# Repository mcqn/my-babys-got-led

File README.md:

# My Babys Got LED

An ESP8266 board to drive Neopixel/WS2812 LED strips, for plug-and-play use with an ATX power supply. The board is [OSHW certified](https://certification.oshwa.org/uk000030.html
). Latest version now has three injection points with 8A fuses for safety, to manage the high power of ATX power supplies.

See the [My Baby's Got LED product page](https://mcqn.com/ibal223) on the MCQN website for full details.

The finished product is available for sale on Tindie:

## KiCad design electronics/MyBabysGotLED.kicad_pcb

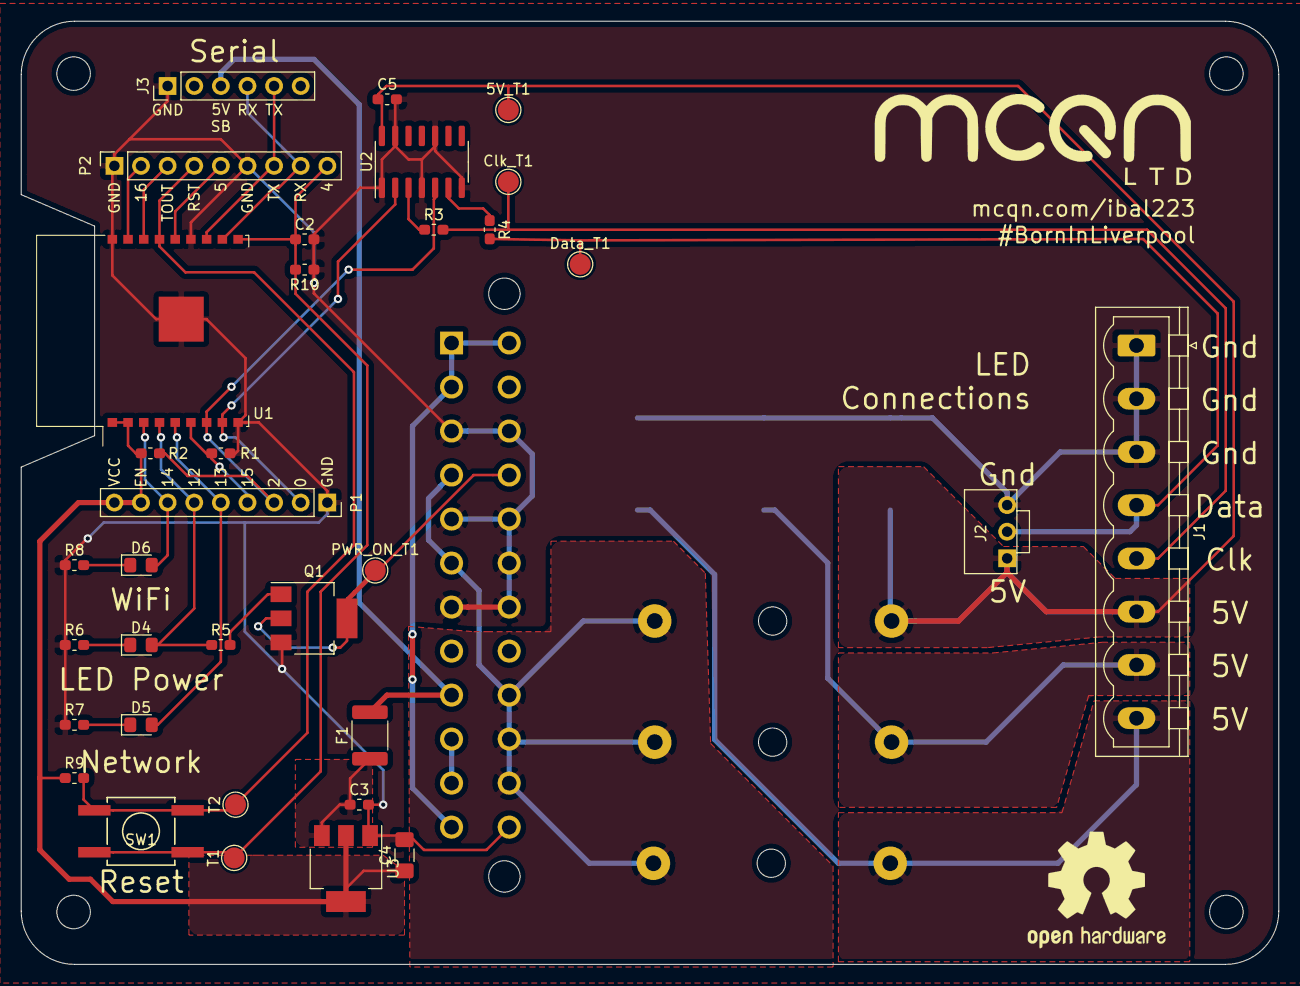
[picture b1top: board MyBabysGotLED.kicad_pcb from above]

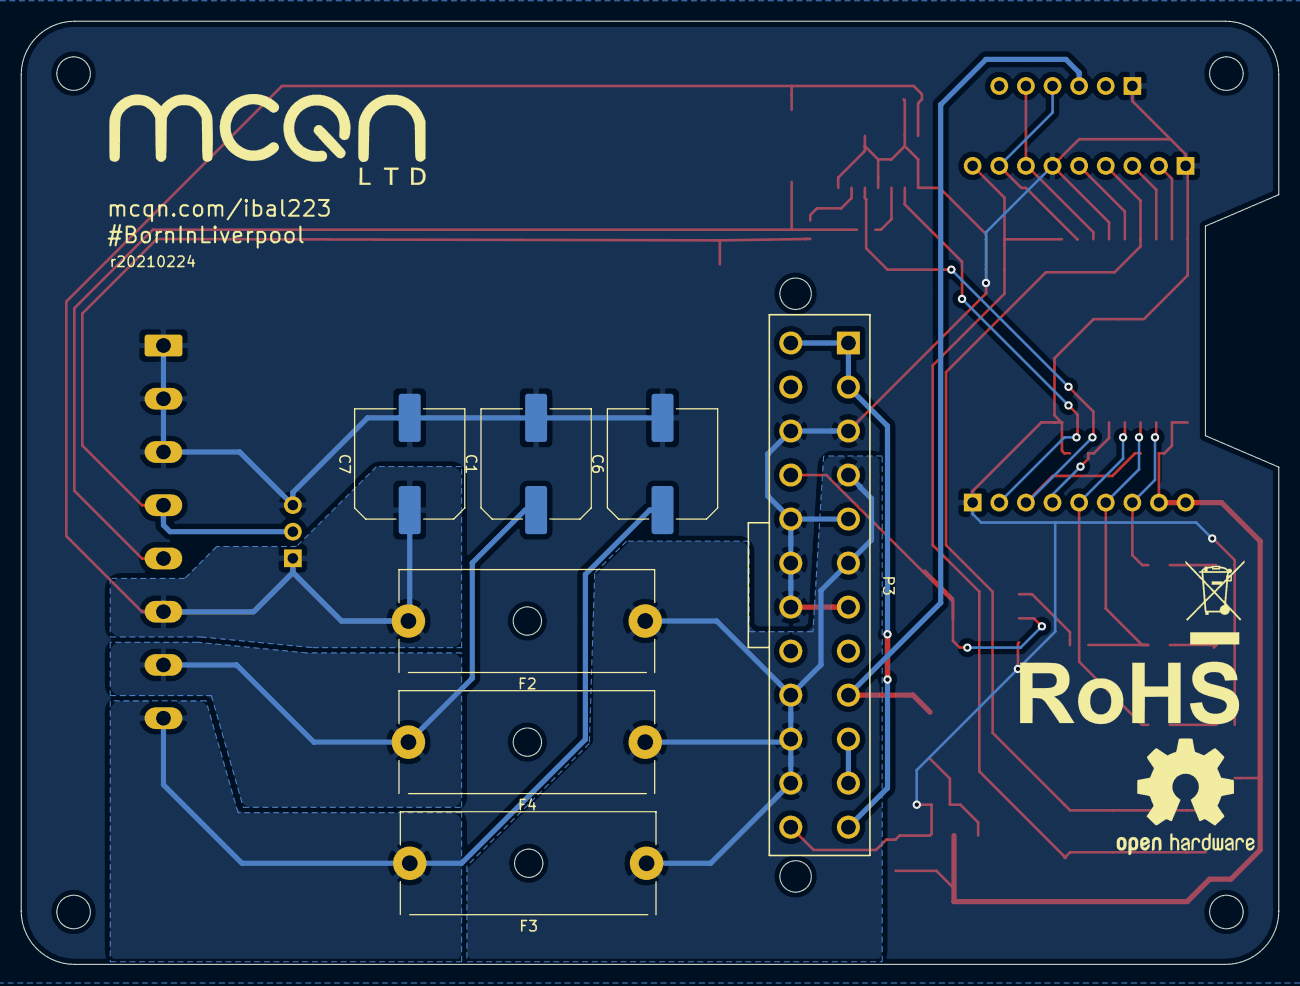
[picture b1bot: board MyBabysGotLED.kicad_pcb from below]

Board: 2 copper layers, 120.0 x 90.0 mm, 41 parts (7 on the bottom side), 32 nets.

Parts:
5V_T1: Conn_01x01; TestPoint_Pad_D2.0mm
C1, C6, C7: 470uF; C_Elec_10x10.2
C2: C47nF; C_0603_1608Metric_Pad1.05x0.95mm_HandSolder
C3, C5: 0.1uF; C_0603_1608Metric_Pad1.05x0.95mm_HandSolder
C4: 10uF; C_1206_3216Metric_Pad1.42x1.75mm_HandSolder
Clk_T1: Conn_01x01; TestPoint_Pad_D2.0mm
D4, D5, D6: LED; LED_0805_2012Metric_Pad1.15x1.40mm_HandSolder
Data_T1: Conn_01x01; TestPoint_Pad_D2.0mm
F1: Polyfuse; Fuse_1812_4532Metric_Pad1.30x3.40mm_HandSolder
F2, F3, F4: Fuse; Fuseholder_Cylinder-5x20mm_Wurth_WR-FSH_Horizontal
J1: APA102; PhoenixContact_MSTBVA_2,5_8-G-5,08_1x08_P5.08mm_Vertical
J2: WS2812; PinHeader_1x03_P2.54mm_Vertical
J3: Serial; PinHeader_1x06_P2.54mm_Vertical
P1, P2: CONN_01X09; PinSocket_1x09_P2.54mm_Vertical
P3: ATX_Power_2x12_Connector; Molex_44206-0007_socket_(ATX_power)
PWR_ON_T1: Conn_01x01; TestPoint_Pad_D2.0mm
Q1: NJT4031NT1G; SOT-223-3_TabPin2
R1, R2, R10: R10k; R_0603_1608Metric_Pad1.05x0.95mm_HandSolder
R3, R4, R5: 470R; R_0603_1608Metric_Pad1.05x0.95mm_HandSolder
R6, R7, R8, R9: R560; R_0603_1608Metric_Pad1.05x0.95mm_HandSolder
SW1: Reset; SW_SPST_GULLWING
T1, T2: CONN_01X01; TestPoint_Pad_D2.0mm
U1: ESP-13-WROOM-02; ESP-WROOM-02
U2: SN74AHCT125; SOIC-14_3.9x8.7mm_P1.27mm
U3: LM1117-3.3; SOT-223-3_TabPin2

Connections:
+3V3: C4.1, P1.8, P1.9, R2.1, R9.1, U1.1, U1.2, U3.2
+5V: F2.1, F3.1, F4.1, P3.4, P3.6, P3.21, P3.22, P3.23
/BaseESP8266/IO4: C2.1, P2.9, R10.2, SW1.1, T1.1, U1.10
/BaseESP8266/IO5: P2.5, U1.14
/BaseESP8266/IO12: D4.2, P1.6, R5.1, U1.4
/BaseESP8266/IO13: D5.2, P1.5, U1.5
/BaseESP8266/IO14: D6.2, P1.7, U1.3
/BaseESP8266/IO15: P1.4, R1.2, U1.6
/BaseESP8266/IO16: P2.2, U1.17
/BaseESP8266/RST: P2.4, R9.2, SW1.2, T2.1, U1.15
/BaseESP8266/RXD: J3.4, P2.8, U1.11
/BaseESP8266/TOUT: P2.3, U1.16
/BaseESP8266/TXD: J3.5, P2.7, U1.12
GND: C1.2, C2.2, C3.2, C4.2, C5.2, C6.2, C7.2, J1.1, J1.2, J1.3, J2.3, J3.1, P1.1, P2.1, P2.6, P3.3, P3.5, P3.7, P3.15, P3.17, P3.18, P3.19, P3.24, Q1.3, R1.1, R6.1, R7.1, R8.1, R10.1, U1.9, U1.13, U1.18, U1.19, U2.1, U2.4, U2.7, U2.10, U2.13, U3.1
LED_Clk: P1.2, U1.8, U2.2
LED_Data: P1.3, R2.2, U1.7, U2.5
unnamed: 5V_T1.1, C5.1, C7.1, F2.2, J1.6, J2.1, U2.14
unnamed: C1.1, F4.2, J1.7
unnamed: C3.1, F1.1, U3.3
unnamed: C6.1, F3.2, J1.8
unnamed: Clk_T1.1, J1.5, R3.2
unnamed: D4.1, R6.2
unnamed: D5.1, R7.2
unnamed: D6.1, R8.2
unnamed: Data_T1.1, J1.4, J2.2, R4.2
unnamed: F1.2, J3.3, P3.9
unnamed: P3.1, P3.2, P3.12, P3.13
unnamed: P3.10, P3.11
unnamed: P3.16, PWR_ON_T1.1, Q1.2
unnamed: Q1.1, R5.2
unnamed: R3.1, U2.3
unnamed: R4.1, U2.6

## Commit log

2020-10-28 Most of schematic laid out. Part of #3, and first pass at #2
2020-10-28 Most of BoM details added. Part of #4
2020-11-02 Add links to the main product page to the readme.
2020-11-04 PCB laid out. Final part of #3 and all of #5
2020-11-06 Update purchase details to PayPal, while we wait for PCBs to arrive for the photo for the Tindie store.
2020-11-06 Add a picture of the finished PCB
2021-02-10 Relicense to CERN-OHL-S v2.0. Part of #9
2021-02-10 Fix image, and add (I hope) Tindie badge.
2021-02-17 Update one of the caps to cut-tape part rather than full reel. Other minor tweaks.
2021-02-26 Board mods to use lower value fuses (rather than a single large fuse). Fixes #14
    * Three 5V/Gnd feeds rather than one, each protected with a 5x20mm 8A fuse
    * 470uF smoothing caps on the 5V lines, rather than a single 1000uF
    * New test points for 5V, data and clock lines
2021-03-07 BoM updates after #14 was fixed (and to add a couple of items missed off earlier)
2021-03-07 Correct Farnell part number for the terminal block
2021-03-10 First steps in a possible testing and programming rig. Part of #15
2021-03-17 Add mounting plate (for MBGLv1 boards!). Part of #7
2021-03-22 Add initial version of the instructions. Part of #16
2021-05-17 Updated photos and OSHW mark
2021-05-17 Rotated OSHW mark
2021-05-17 Rearranged readme
2021-05-17 Added some pics
2021-05-17 Corrected typo on the abbreviations in file names
    Embarrassing.
2021-05-17 Fixed broken image link in Readme
2021-05-17 Corrected OSHW certification code
2021-06-08 Added animated gifs of implementations
2021-06-19 Finishing off steps for setting up programming rig. Part of #15
2021-07-13 Renamed ATX mounting plate and added sandwich enclosure
    The sandwich enclosure needs 20mm standoffs for the power side and 10mm standoffs for the LED and status light side.
2021-07-13 Made filenames more specific
2021-07-27 Added & updated mounting boards
    Added one-side board; updated other options after manufacturing them to check dimensions and files; included laser-ready dxf files as well as SVGs; and added some explanatory text in the design files.
2022-04-11 Added board reset to change mDNS name to instructions as #23
2022-05-23 Changed https://github.com/Aircoookie/WLED/wiki to https://kno.wled.ge
2022-05-25 Add updatinging firmware instructions and latest bin
